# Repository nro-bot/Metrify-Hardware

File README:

16 Jan 2012: started on firmware
13 Jan 2012: ordered boards
10 Jan 2012: This repo is for the hardware files (eagle, firmware) for the Metrify project. Eagle version 6 used (not compatible with eagle v5 files)

Time span: January 2012 (IAP).
Hardware team members: mark spatz (mspatz), nancy ouyang (nouyang)
Software members: Diyang Tang (dydt), Cathy Wu (cathywu)

Everything in this git repo, unless otherwise noted, is dedicated to the public domain. Specifically, the license.txt is the CC0 (creative commons zero) 1.0 license.
See: http://creativecommons.org/publicdomain/zero/1.0/
My summary is, do whatever you want with the stuff in here. As a personal favor, if you let us know what's up, that'd be great.
Cheers,
--Nancy

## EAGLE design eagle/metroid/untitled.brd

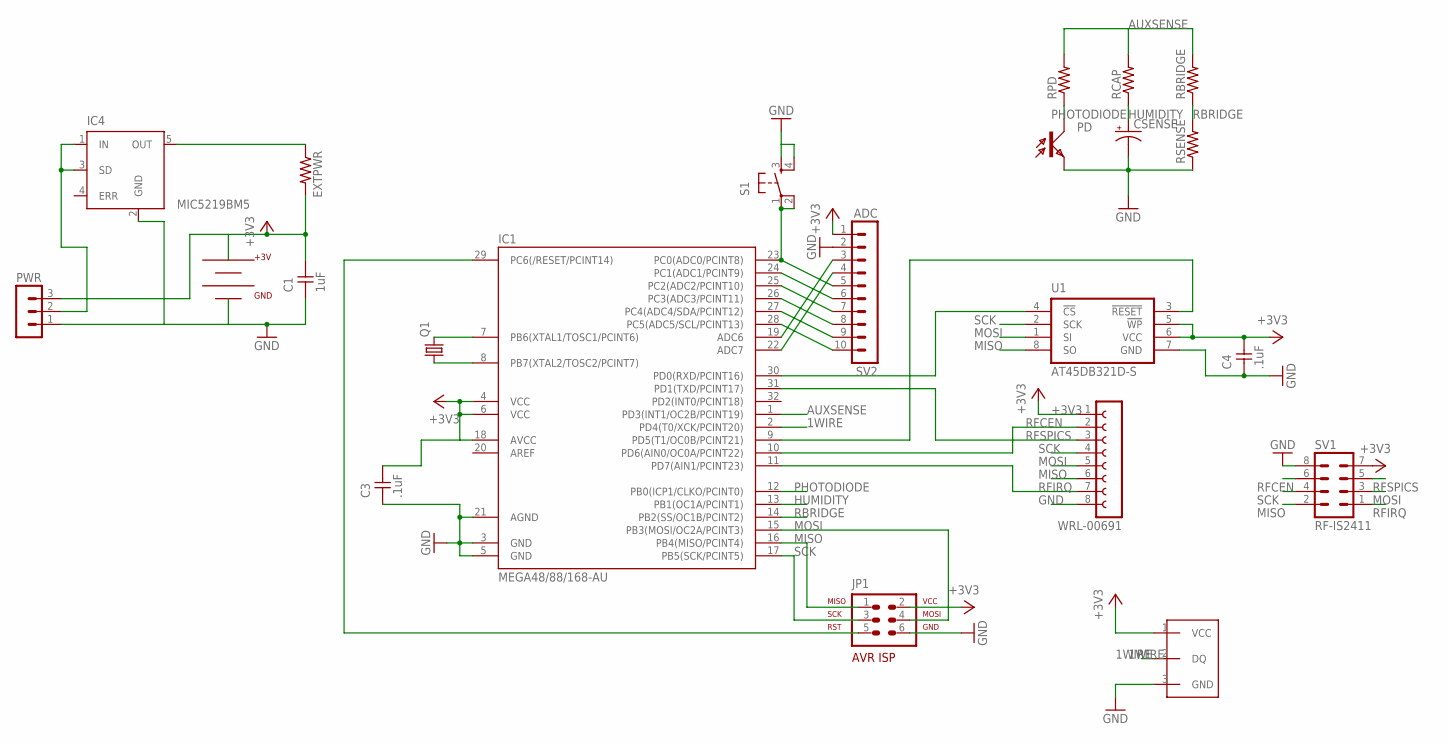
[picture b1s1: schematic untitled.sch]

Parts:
C1: 1uF; 1206
C3, C4: .1uF; 1206
CSENSE: CPOL-USE5-8.5; E5-8,5
EXTPWR: R-US_M0805; M0805
IC1: MEGA48/88/168-AU; TQFP32-08
IC4: MIC5219BM5; SOT23-5
JP1: AVR-ISP; AVR-ISP-6
PD: PHOTOTRANSISTOR5MM; 5MM
PWR: MA03-1
Q1: CRYSTALTC26H; TC26H
RBRIDGE: RESISTOR1206; 1206
RCAP: RESISTOR1206; 1206
RPD: RESISTOR1206; 1206
RSENSE: R-US_0207/7; 0207/7
S1: 6MM_SWITCH6MM_SWITCH; 6MM_SWITCH
SV1: RF-IS2411; MA04-2
SV2: ADC; MA10-1
U1: AT45DB321D-S; SO08-8S2
U$1: BS-7BATTERYCLIP; BS-7PACKAGE
U$2: DS18S20; TO92
WRL-00691: FE08-1; FE08

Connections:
1WIRE: IC1.2 (PD4(T0/XCK/PCINT20)), U$2.2 (DQ)
+3V3: C1.2, C3.2, C4.2, EXTPWR.2, IC1.4 (VCC), IC1.6 (VCC), IC1.18 (AVCC), JP1.2, PWR.3, SV1.7, SV2.1, U1.5 (!WP!), U1.6 (VCC), U$1.POS, U$2.1 (VCC), WRL-00691.1
AUXSENSE: IC1.1 (PD3(INT1/OC2B/PCINT19)), RBRIDGE.2, RCAP.2, RPD.2
GND: C1.1, C3.1, C4.1, CSENSE.-, IC1.3 (GND), IC1.5 (GND), IC1.21 (AGND), IC4.2 (GND), JP1.6, PD.OUT (E), PWR.1, RSENSE.1, S1.3 (S), S1.4 (S1), SV1.8, SV2.2, U1.7 (GND), U$1.NEG, U$2.3 (GND), WRL-00691.8
HUMIDITY: CSENSE.+, IC1.13 (PB1(OC1A/PCINT1)), RCAP.1
MISO: IC1.16 (PB4(MISO/PCINT4)), JP1.1, SV1.2, U1.8 (SO), WRL-00691.6
MOSI: IC1.15 (PB3(MOSI/OC2A/PCINT3)), JP1.4, SV1.3, U1.1 (SI), WRL-00691.5
unnamed: IC1.9 (PD5(T1/OC0B/PCINT21)), U1.3 (!RESET!)
unnamed: IC1.7 (PB6(XTAL1/TOSC1/PCINT6)), Q1.2
unnamed: IC1.8 (PB7(XTAL2/TOSC2/PCINT7)), Q1.1
unnamed: EXTPWR.1, IC4.5 (OUT)
unnamed: IC1.23 (PC0(ADC0/PCINT8)), S1.1, S1.2 (P1), SV2.5
unnamed: IC1.24 (PC1(ADC1/PCINT9)), SV2.6
unnamed: IC1.25 (PC2(ADC2/PCINT10)), SV2.7
unnamed: IC1.26 (PC3(ADC3/PCINT11)), SV2.8
unnamed: IC1.27 (PC4(ADC4/SDA/PCINT12)), SV2.9
unnamed: IC1.28 (PC5(ADC5/SCL/PCINT13)), SV2.10
unnamed: IC1.22 (ADC7), SV2.4
unnamed: IC4.1 (IN), IC4.3 (SD), PWR.2
unnamed: IC1.19 (ADC6), SV2.3
PHOTODIODE: IC1.12 (PB0(ICP1/CLKO/PCINT0)), PD.IN (C), RPD.1
PORTC: IC1.30 (PD0(RXD/PCINT16)), U1.4 (!CS!)
RBRIDGE: IC1.14 (PB2(SS/OC1B/PCINT2)), RBRIDGE.1, RSENSE.2
RESET: IC1.29 (PC6(/RESET/PCINT14)), JP1.5
RFCEN: IC1.10 (PD6(AIN0/OC0A/PCINT22)), SV1.6, WRL-00691.2
RFIRQ: IC1.11 (PD7(AIN1/PCINT23)), SV1.1, WRL-00691.7
RFSPICS: IC1.31 (PD1(TXD/PCINT17)), SV1.5, WRL-00691.3
SCK: IC1.17 (PB5(SCK/PCINT5)), JP1.3, SV1.4, U1.2 (SCK), WRL-00691.4

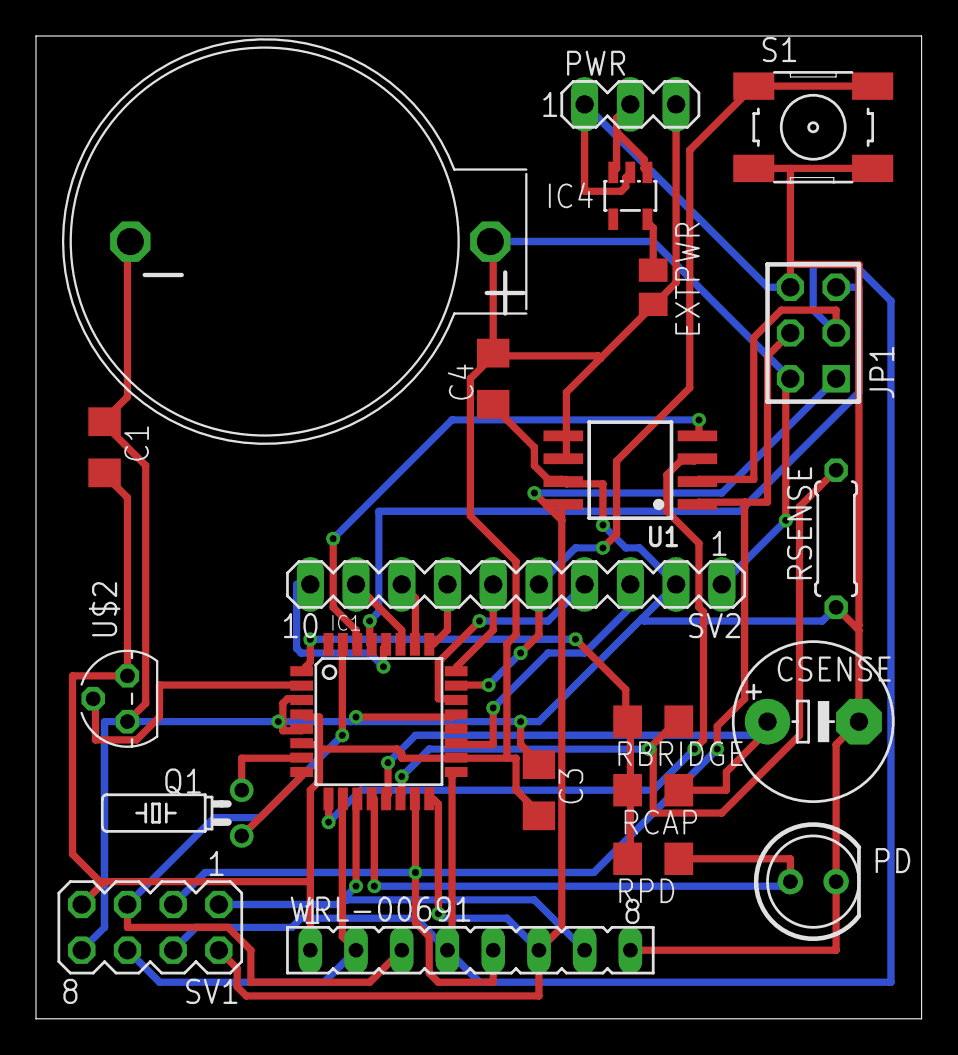
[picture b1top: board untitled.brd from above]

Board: 2 copper layers, 49.2 x 54.6 mm, 22 parts (0 on the bottom side), 28 nets.

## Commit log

2012-01-10 troll commit.
2012-01-10 mspatz's eagle files
2012-01-11 mspatz's work for the day
2012-01-12 before adding humidity
2012-01-13 board routed. eagle 6. 6 mil traces, qfp atmega+battery+labpowerheaders+headers>sparkfunnordic or mdfly+pads for 1206 sensors, humidity, phototransistor+isp+pushbutton
2012-01-16 ordered barebones boards from 4pcb, added sch screenshot
2012-01-17 mspatz: beginnings of firmware. me: license+readme update
2012-01-17 readme fix
2012-01-17 test board + firware for ftdi serial out
2012-01-17 merge? test commit
2012-01-18 mspatz: readings+beginning wireless firmware
2012-01-18 mspatz working snapshot
2012-01-18 snapshot, mspatz's work
2012-01-19 Button Counting works
2012-01-19 serial read to text file for demo today
2012-01-19 demo button press count + time (preprocessed on receiver side before polled by database)

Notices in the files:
parts and their libraries:
memory-atmel: Copyright (C) 2008, Bob Starr
